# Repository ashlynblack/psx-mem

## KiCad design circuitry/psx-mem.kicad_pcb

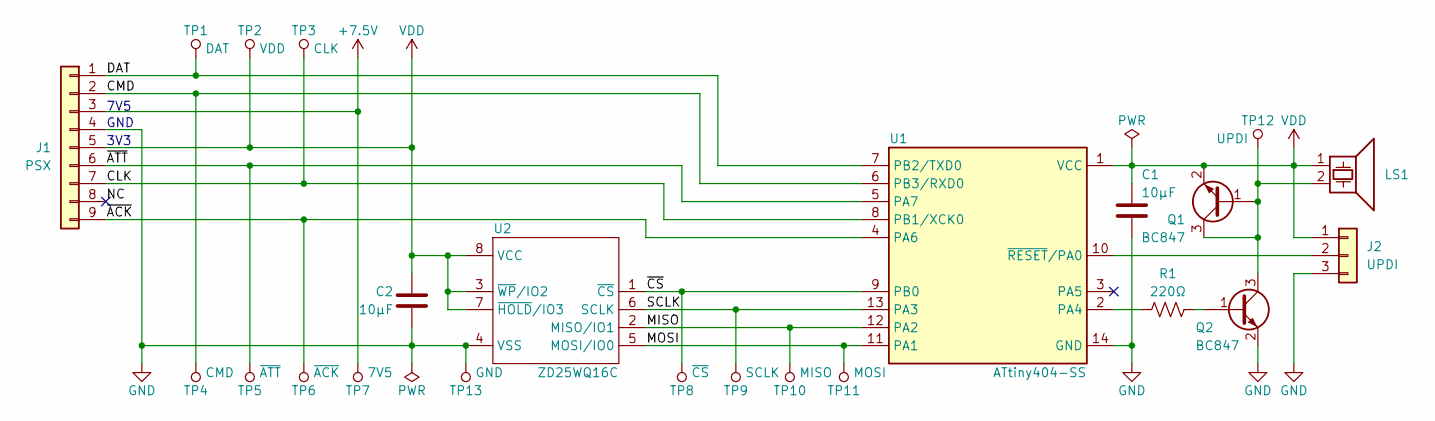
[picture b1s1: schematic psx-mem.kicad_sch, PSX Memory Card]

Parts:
C1, C2: 10µF; C_0805_2012Metric
J1: Conn_01x08; PSX_Connector
J2: Conn_01x03; TestPoint_UPDI
LS1: Speaker_Crystal; BUZ-SMD_4P-L7.5-W7.5-BR
Q1, Q2: BC847; SOT-23-3
R1: 220Ω; R_0805_2012Metric
TP1, TP2, TP3, TP4, TP5, TP6, TP7, TP8, TP9, TP10, TP11, TP12, TP13: TestPoint; TestPoint_Pad_D1.0mm
U1: ATtiny404-SS; SOIC-14_3.9x8.7mm_P1.27mm
U2: ZD25WQ16C; SOIC-8_3.9x4.9mm_P1.27mm

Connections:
+7.5V: J1.3, TP7.1
/CLK: J1.7, TP3.1, U1.8 (PB1/XCK0)
/CMD: J1.2, TP4.1, U1.6 (PB3/RXD0)
/DAT: J1.1, TP1.1, U1.7 (PB2/TXD0)
/MISO: TP10.1, U1.12 (PA2), U2.2 (MISO/IO1)
/MOSI: TP11.1, U1.11 (PA1), U2.5 (MOSI/IO0)
/SCLK: TP9.1, U1.13 (PA3), U2.6 (SCLK)
/~ACK: J1.9, TP6.1, U1.4 (PA6)
/~ATT: J1.6, TP5.1, U1.5 (PA7)
/~CS: TP8.1, U1.9 (PB0), U2.1 (~CS)
GND: C1.2, C2.2, J1.4, J2.3, Q2.2 (E), TP13.1, U1.14 (GND), U2.4 (VSS)
unnamed: J2.2, U1.10 (~RESET/PA0)
unnamed: LS1.2, Q1.1 (B), Q1.3 (C), Q2.3 (C), TP12.1
unnamed: Q2.1 (B), R1.2
unnamed: R1.1, U1.2 (PA4)
VDD: C1.1, C2.1, J1.5, J2.1, LS1.1, Q1.2 (E), TP2.1, U1.1 (VCC), U2.3 (~WP/IO2), U2.7 (~HOLD/IO3), U2.8 (VCC)

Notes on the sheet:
GND
3V3
7V5

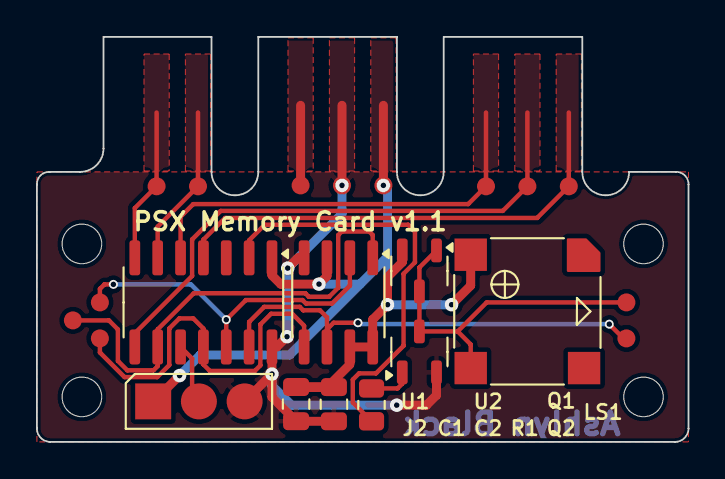
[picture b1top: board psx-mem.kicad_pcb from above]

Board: 2 copper layers, 36.2 x 22.5 mm, 22 parts (0 on the bottom side), 15 nets.

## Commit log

2024-07-09 Started Git ignore list.
2024-07-09 Tracked PDF, PNG, ZIP and JPGs with Git LFS.
2024-07-09 Added datasheets, application notes and user manuals to research.
2024-07-09 Completed schematic and layout.
2024-07-09 Rendered model, generated BOM, gerbers, schematic and layout.
2024-07-09 Added handwritten notes to research.
2024-07-10 Generated interactive bill of materials.
2024-07-19 Updated to use libraries in submodules.
2024-07-27 Ignored KiCAD backup files.
2024-07-27 Updated datasheets.
2024-07-27 Schematic and layout completed.
2024-07-27 Generated project artifacts.
